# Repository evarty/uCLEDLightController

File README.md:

This is the hardware and software for a simply Attiny45 based TM1803 LED strip. It only provides off and white light.
The hardware files are KiCAD and currently only include a minimal schematic.

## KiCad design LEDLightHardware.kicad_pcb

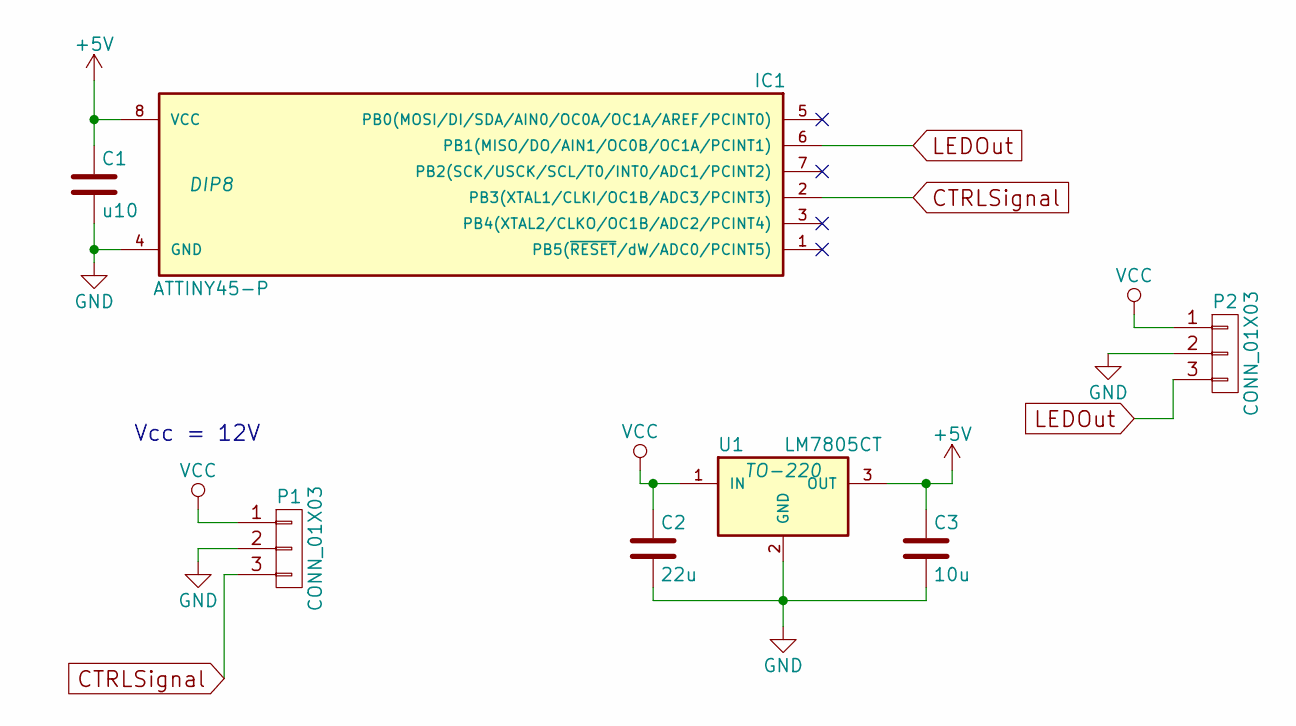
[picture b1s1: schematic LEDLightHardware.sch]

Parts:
C1: u10
C2: 22u
C3: 10u
IC1: ATTINY45-P; DIP8
P1, P2: CONN_01X03
U1: LM7805CT; TO-220

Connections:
+5V: C1.1, C3.1, IC1.8 (VCC), U1.3 (OUT)
CTRLSignal: IC1.2 (PB3(XTAL1/CLKI/OC1B/ADC3/PCINT3)), P1.3
GND: C1.2, C2.2, C3.2, IC1.4 (GND), P1.2, P2.2, U1.2 (GND)
LEDOut: IC1.6 (PB1(MISO/DO/AIN1/OC0B/OC1A/PCINT1)), P2.3
VCC: C2.1, P1.1, P2.1, U1.1 (IN)

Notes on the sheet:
Vcc = 12V

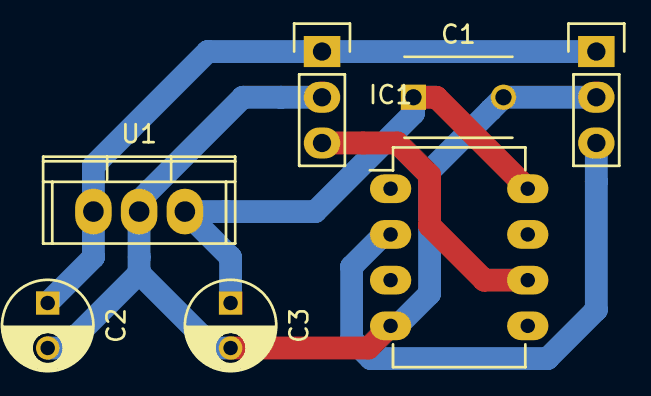
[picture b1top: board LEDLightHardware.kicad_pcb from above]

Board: 2 copper layers, 7 parts (0 on the bottom side), 5 nets.

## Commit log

2016-04-03 Inital commit
2016-04-03 Added power input and regulation
2016-04-03 added pdf schematic
2016-04-03 fixed pdf schematic
2016-04-08 Reorganized
2016-04-22 Moved board files to new directory
2016-04-22 changed filename
